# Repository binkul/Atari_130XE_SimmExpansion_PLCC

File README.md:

# KiCad files for:
# Atari 130 XE Simm Expansion - 1 mb os SDRAM
## Gal20V8 in PLCC28
## This is an upgrade of Atari 130XE with 4 banks of 4464
## GAL content.jed -> jedec file for GAL 20V8

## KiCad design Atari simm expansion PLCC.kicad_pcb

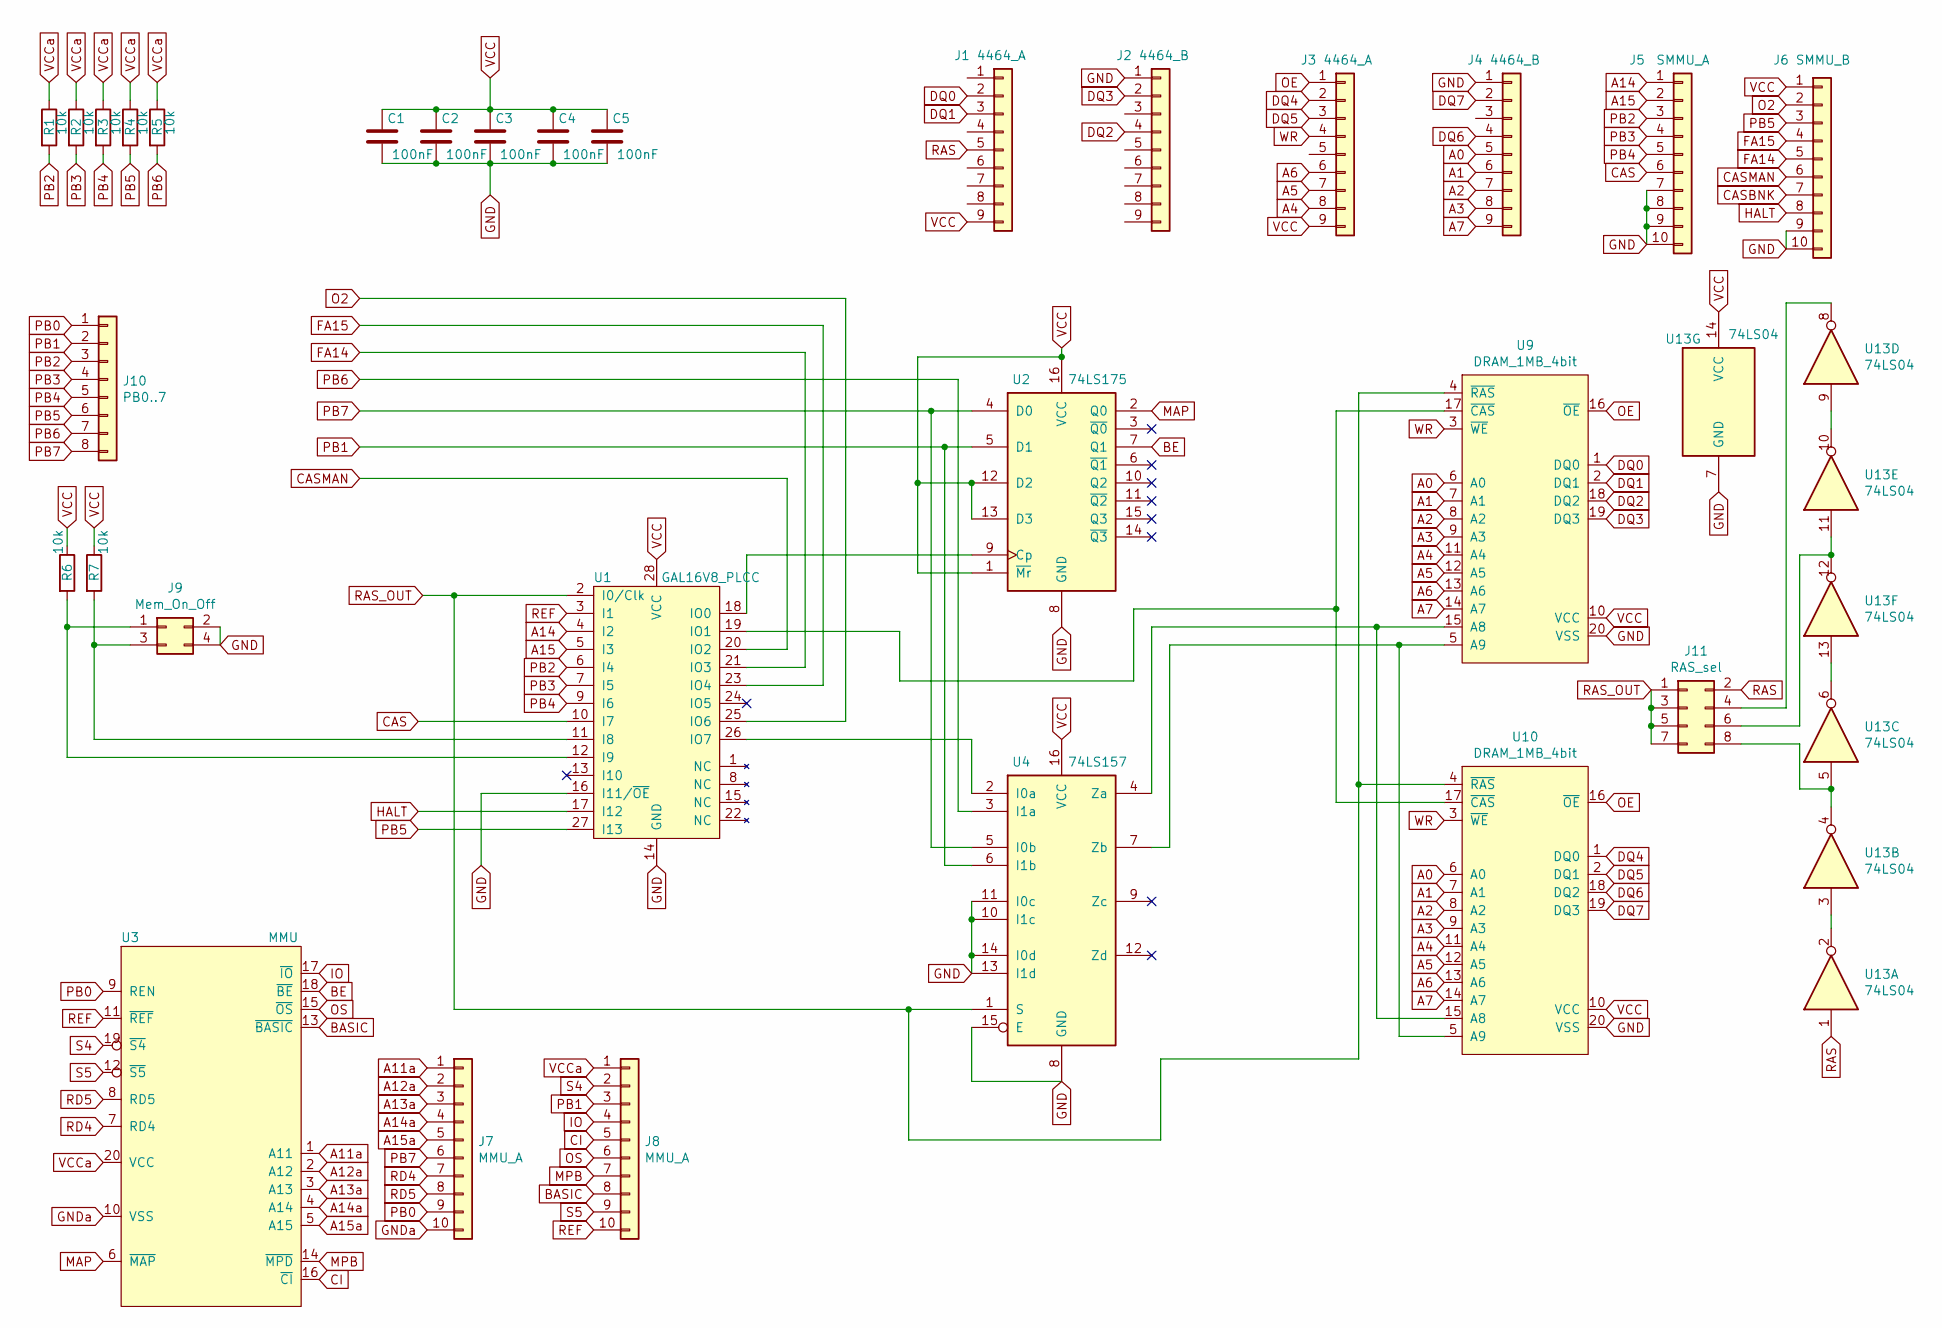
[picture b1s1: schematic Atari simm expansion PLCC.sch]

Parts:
C1, C2, C3, C4, C5: 100nF; C_1206_3216Metric_Pad1.42x1.75mm_HandSolder
J1, J3: 4464_A; PinHeader_1x09_P2.54mm_Vertical
J2, J4: 4464_B; PinHeader_1x09_P2.54mm_Vertical
J5: SMMU_A; PinHeader_1x10_P2.54mm_Vertical
J6: SMMU_B; PinHeader_1x10_P2.54mm_Vertical
J7, J8: MMU_A; PinHeader_1x10_P2.54mm_Vertical
J9: Mem_On_Off; PinHeader_2x02_P2.54mm_Vertical
J10: PB0..7; PinHeader_1x08_P2.54mm_Vertical
J11: RAS_sel; PinHeader_2x04_P2.00mm_Vertical
R1, R2, R3, R4, R5, R6, R7: 10k; R_1206_3216Metric_Pad1.42x1.75mm_HandSolder
U1: GAL16V8_PLCC; PLCC-28
U2: 74LS175; SOP-16_4.4x10.4mm_P1.27mm
U3: MMU; DIP-20_W7.62mm_Socket
U4: 74LS157; SOP-16_4.4x10.4mm_P1.27mm
U9, U10: DRAM_1MB_4bit; SOJ-26
U13: 74LS04; SOIC-14_3.9x8.7mm_P1.27mm

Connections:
A0: J4.5, U9.6 (A0), U10.6 (A0)
A1: J4.6, U9.7 (A1), U10.7 (A1)
A2: J4.7, U9.8 (A2), U10.8 (A2)
A3: J4.8, U9.9 (A3), U10.9 (A3)
A4: J3.8, U9.11 (A4), U10.11 (A4)
A5: J3.7, U9.12 (A5), U10.12 (A5)
A6: J3.6, U9.13 (A6), U10.13 (A6)
A7: J4.9, U9.14 (A7), U10.14 (A7)
A11a: J7.1, U3.1 (A11)
A12a: J7.2, U3.2 (A12)
A13a: J7.3, U3.3 (A13)
A14: J5.1, U1.4 (I2)
A14a: J7.4, U3.4 (A14)
A15: J5.2, U1.5 (I3)
A15a: J7.5, U3.5 (A15)
BASIC: J8.8, U3.13 (~BASIC)
BE: U2.7 (Q1), U3.18 (~BE)
CAS: J5.6, U1.10 (I7)
CASMAN: J6.6, U1.20 (IO2)
CI: J8.5, U3.16 (~CI)
DQ0: J1.2, U9.1 (DQ0)
DQ1: J1.3, U9.2 (DQ1)
DQ2: J2.4, U9.18 (DQ2)
DQ3: J2.2, U9.19 (DQ3)
DQ4: J3.2, U10.1 (DQ0)
DQ5: J3.3, U10.2 (DQ1)
DQ6: J4.4, U10.18 (DQ2)
DQ7: J4.2, U10.19 (DQ3)
FA14: J6.5, U1.21 (IO3)
FA15: J6.4, U1.23 (IO4)
GND: C1.2, C2.2, C3.2, C4.2, C5.2, J2.1, J4.1, J5.7, J5.8, J5.9, J5.10, J6.9, J6.10, J9.2, J9.4, U1.14 (GND), U1.16 (I11/~OE), U2.8 (GND), U4.8 (GND), U4.10 (I1c), U4.11 (I0c), U4.13 (I1d), U4.14 (I0d), U4.15 (E), U9.20 (VSS), U10.20 (VSS), U13.7 (GND)
GNDa: J7.10, U3.10 (VSS)
HALT: J6.8, U1.17 (I12)
IO: J8.4, U3.17 (~IO)
MAP: U2.2 (Q0), U3.6 (~MAP)
MPB: J8.7, U3.14 (~MPD)
unnamed: J9.1, R6.2, U1.12 (I9)
unnamed: J9.3, R7.2, U1.11 (I8)
unnamed: J11.4, U13.8
unnamed: J11.6, U13.11, U13.12
unnamed: J11.8, U13.4, U13.5
unnamed: U1.18 (IO0), U2.9 (Cp)
unnamed: U1.19 (IO1), U9.17 (~CAS), U10.17 (~CAS)
unnamed: U1.26 (IO7), U4.2 (I0a)
unnamed: U4.7 (Zb), U9.5 (A9), U10.5 (A9)
unnamed: U4.4 (Za), U9.15 (A8), U10.15 (A8)
unnamed: U13.2, U13.3
unnamed: U13.9, U13.10
unnamed: U13.6, U13.13
O2: J6.2, U1.25 (IO6)
OE: J3.1, U9.16 (~OE), U10.16 (~OE)
OS: J8.6, U3.15 (~OS)
PB0: J7.9, J10.1, U3.9 (REN)
PB1: J8.3, J10.2, U2.5 (D1), U4.6 (I1b)
PB2: J5.3, J10.3, R1.2, U1.6 (I4)
PB3: J5.4, J10.4, R2.2, U1.7 (I5)
PB4: J5.5, J10.5, R3.2, U1.9 (I6)
PB5: J6.3, J10.6, R4.2, U1.27 (I13)
PB6: J10.7, R5.2, U4.3 (I1a)
PB7: J7.6, J10.8, U2.4 (D0), U4.5 (I0b)
RAS: J1.5, J11.2, U13.1
RAS_OUT: J11.1, J11.3, J11.5, J11.7, U1.2 (I0/Clk), U4.1 (S), U9.4 (~RAS), U10.4 (~RAS)
RD4: J7.7, U3.7 (RD4)
RD5: J7.8, U3.8 (RD5)
REF: J8.10, U1.3 (I1), U3.11 (~REF)
S4: J8.2, U3.19 (~S4)
S5: J8.9, U3.12 (~S5)
VCC: C1.1, C2.1, C3.1, C4.1, C5.1, J1.9, J3.9, J6.1, R6.1, R7.1, U1.28 (VCC), U2.1 (~Mr), U2.12 (D2), U2.13 (D3), U2.16 (VCC), U4.16 (VCC), U9.10 (VCC), U10.10 (VCC), U13.14 (VCC)
VCCa: J8.1, R1.1, R2.1, R3.1, R4.1, R5.1, U3.20 (VCC)
WR: J3.4, U9.3 (~WE), U10.3 (~WE)

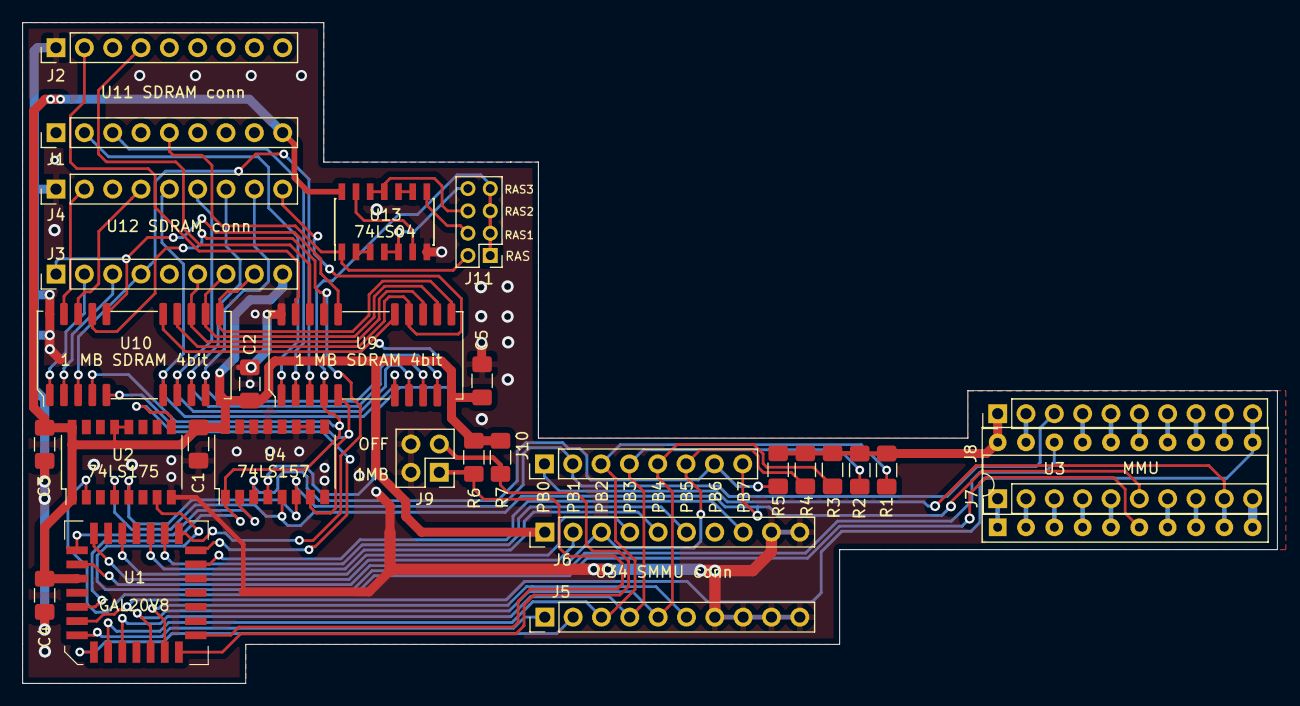
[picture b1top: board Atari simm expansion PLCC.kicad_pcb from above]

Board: 2 copper layers, 112.5 x 59.2 mm, 30 parts (0 on the bottom side), 70 nets.

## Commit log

2021-02-28 Full commit
2021-03-01 Add jedec file for gal
2021-03-18 Tracking
